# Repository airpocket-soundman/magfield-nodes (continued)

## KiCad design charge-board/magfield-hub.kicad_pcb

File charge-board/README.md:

# 充電ボード（ハブ）

ノード基板10台分の充電・監視・書き込みをまとめるボードです。KiCadファイル一式を追加済みですが、**まだ設計途中（WIP）で未発注**です。詳細は [DESIGN.md](DESIGN.md) を参照してください。

## ステータス（2026-10-30時点）

- 4層基板（100 × 96 mm）。現行ファイル（routed70）のDRCは、未接続1件（U2 TCA9535 の VCC）と CH6_STAT ビアのクリアランスエラー4件が残っています。
- U2周りの局部改版は試行済みですが、最良案は採用せず現行ファイルのままです。対処方針は DESIGN.md に記録しています。
- `wip/magfield-hub-u2rev19-WIP.kicad_pcb` は、そのU2改版の試行版（設計途中の作業ファイル）です。クリアランスエラーは0件まで解消しましたが、信号の未接続が6件残っており、現行ファイルには未反映です。

## 構成

- ホスト接続: M5Stack の Port A（Grove / I2C）。ボード自体にマイコンは載せない
- 充電チャンネル ×10: MCP73831（PROG抵抗で約40mA = LIR2032の1C）、チャンネルごとのカットオフ用MOSFETとステータスLED
- 制御・監視: TCA9535（I2C GPIOエクスパンダ）×2 でカットオフ制御とSTAT読み取り、74HC4067（アナログマルチプレクサ）+ ADS1115（I2C ADC）で全チャンネルの電池電圧を読み取り
  - 「充電を一瞬止めてから電圧を測る」ことで、80〜90%充電でのカットオフを電圧ベースで判定する
- 書き込み: UPDI入力を同様に切り替えて、選択したチャンネルのノードへ書き込み信号を送る
- 電源: 充電用5VはボードのUSB-C入力から（10ch合計約400mAのため、Port Aの5Vには頼らない）
- ノード接続: JST PH 4ピン ×10（1=GND / 2=VBAT充電 / 3=UPDI / 4=ID予備）— ノード基板側と同一の割り当て

## ファイル

- `magfield-hub.kicad_pro / .kicad_sch / .kicad_pcb` — KiCad 8 プロジェクト
- `DESIGN.md` — 設計仕様・判断記録・検証結果
- `hub-bom-jlcpcb.csv` / `hub-cpl-jlcpcb.csv` — JLCPCB PCBA用BOM・配置データ
- `gerbers/` — 製造用ガーバー（4層）

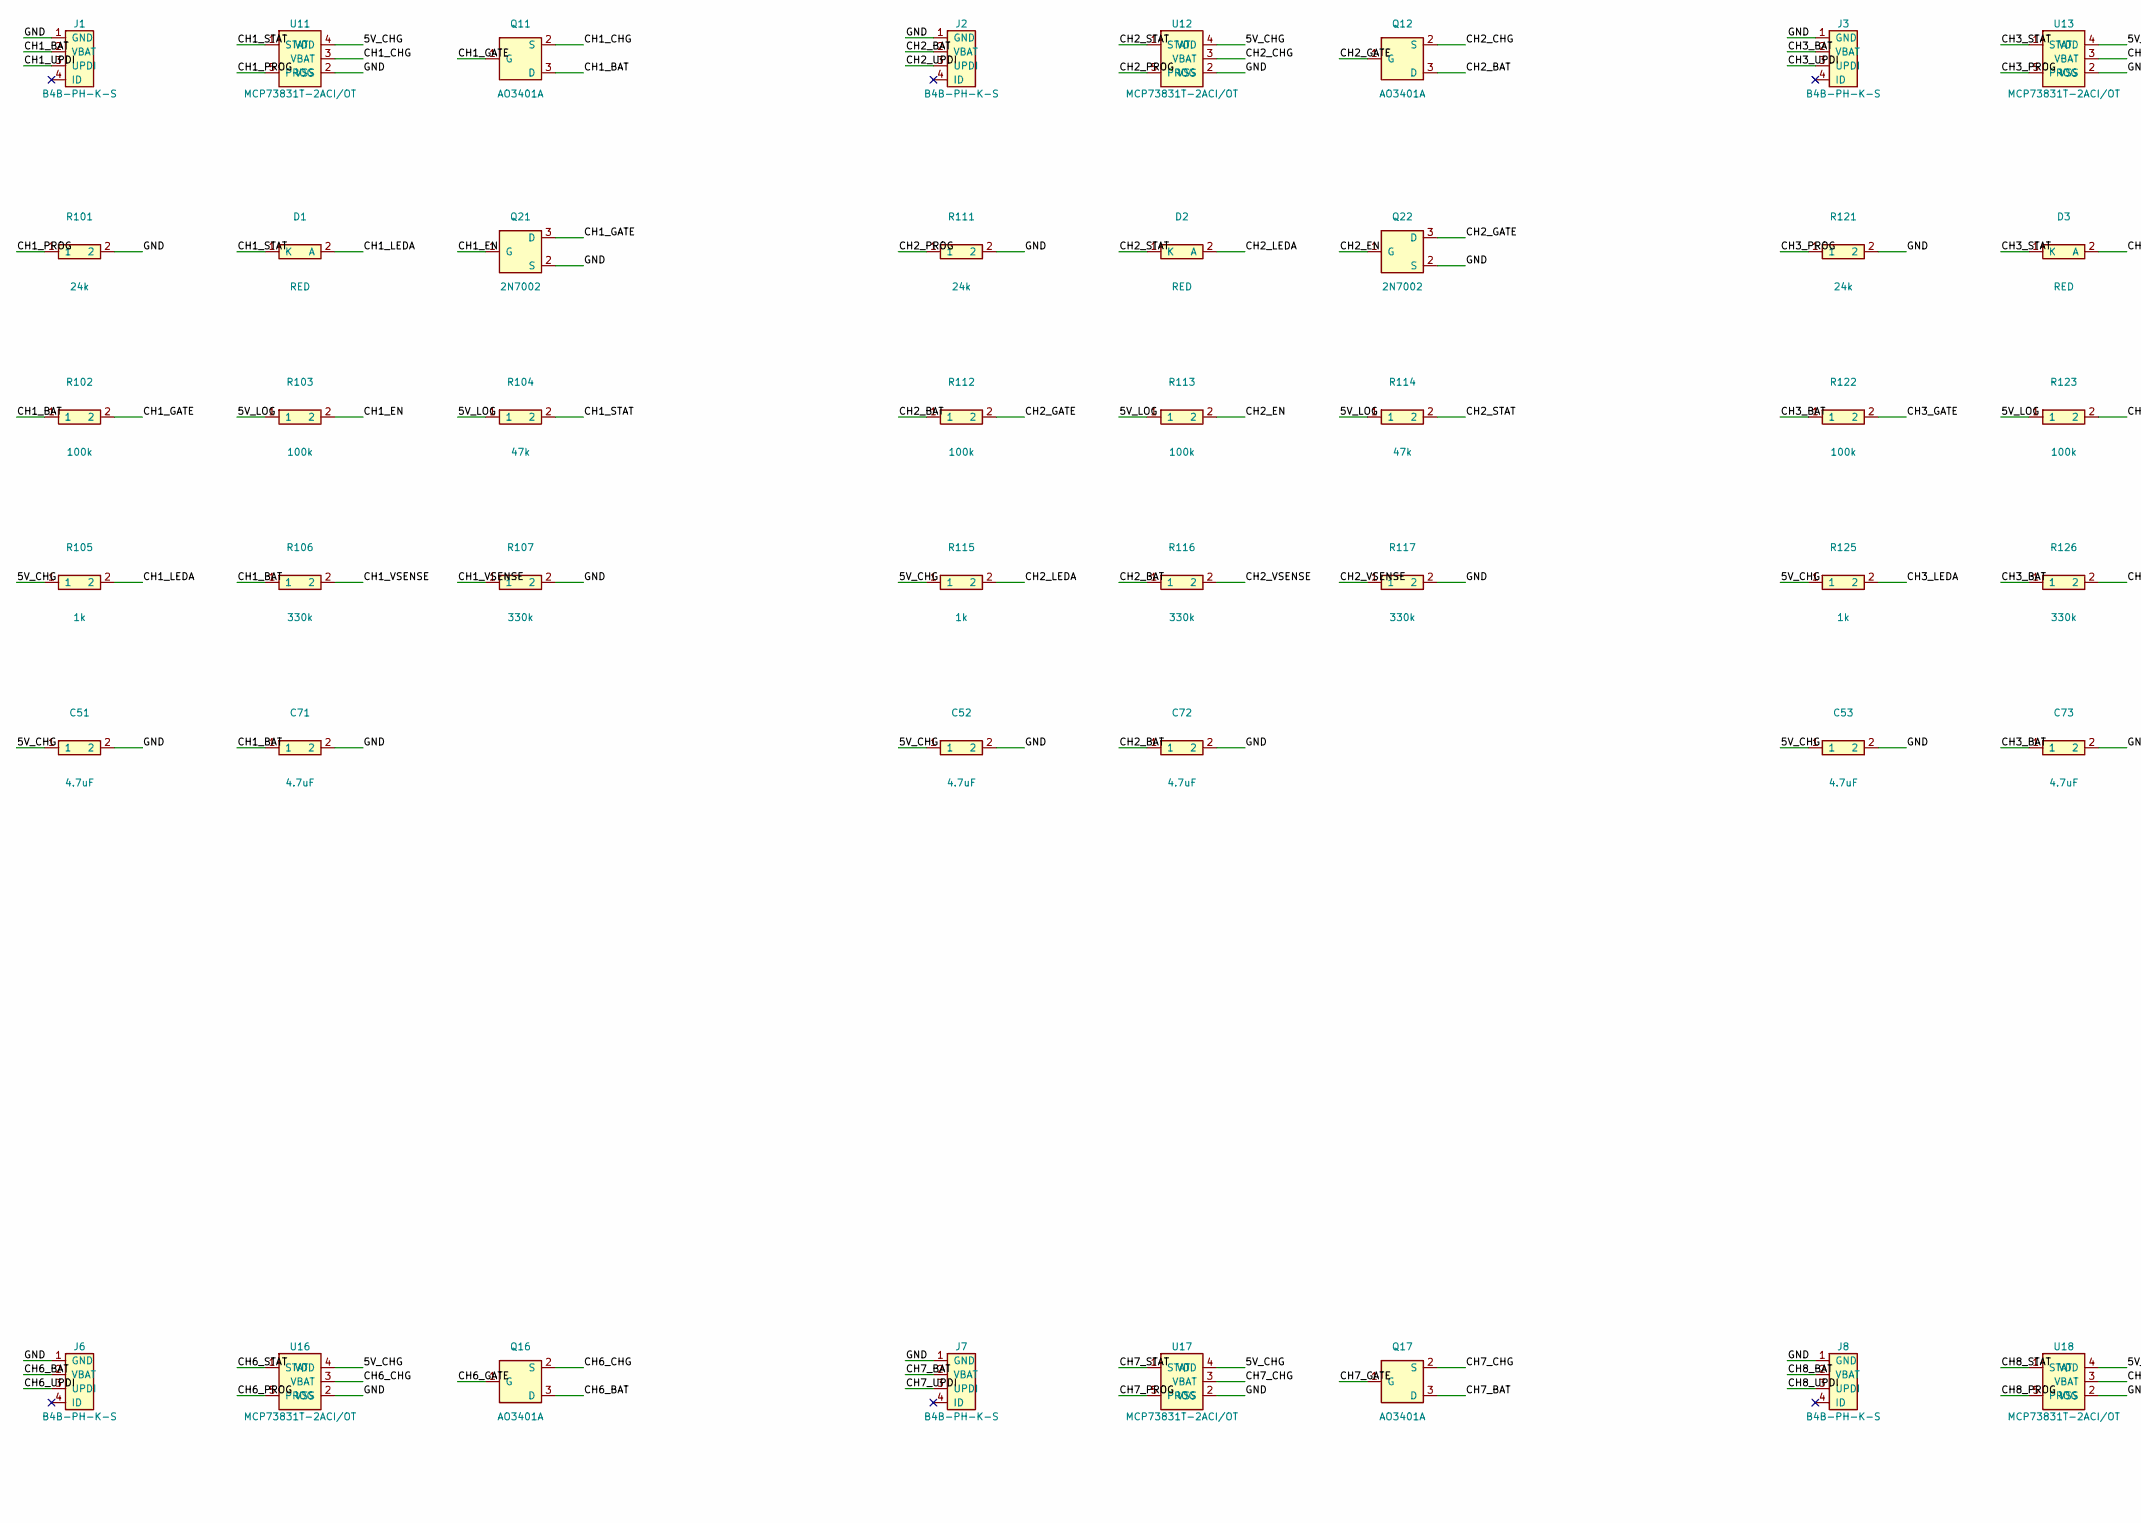
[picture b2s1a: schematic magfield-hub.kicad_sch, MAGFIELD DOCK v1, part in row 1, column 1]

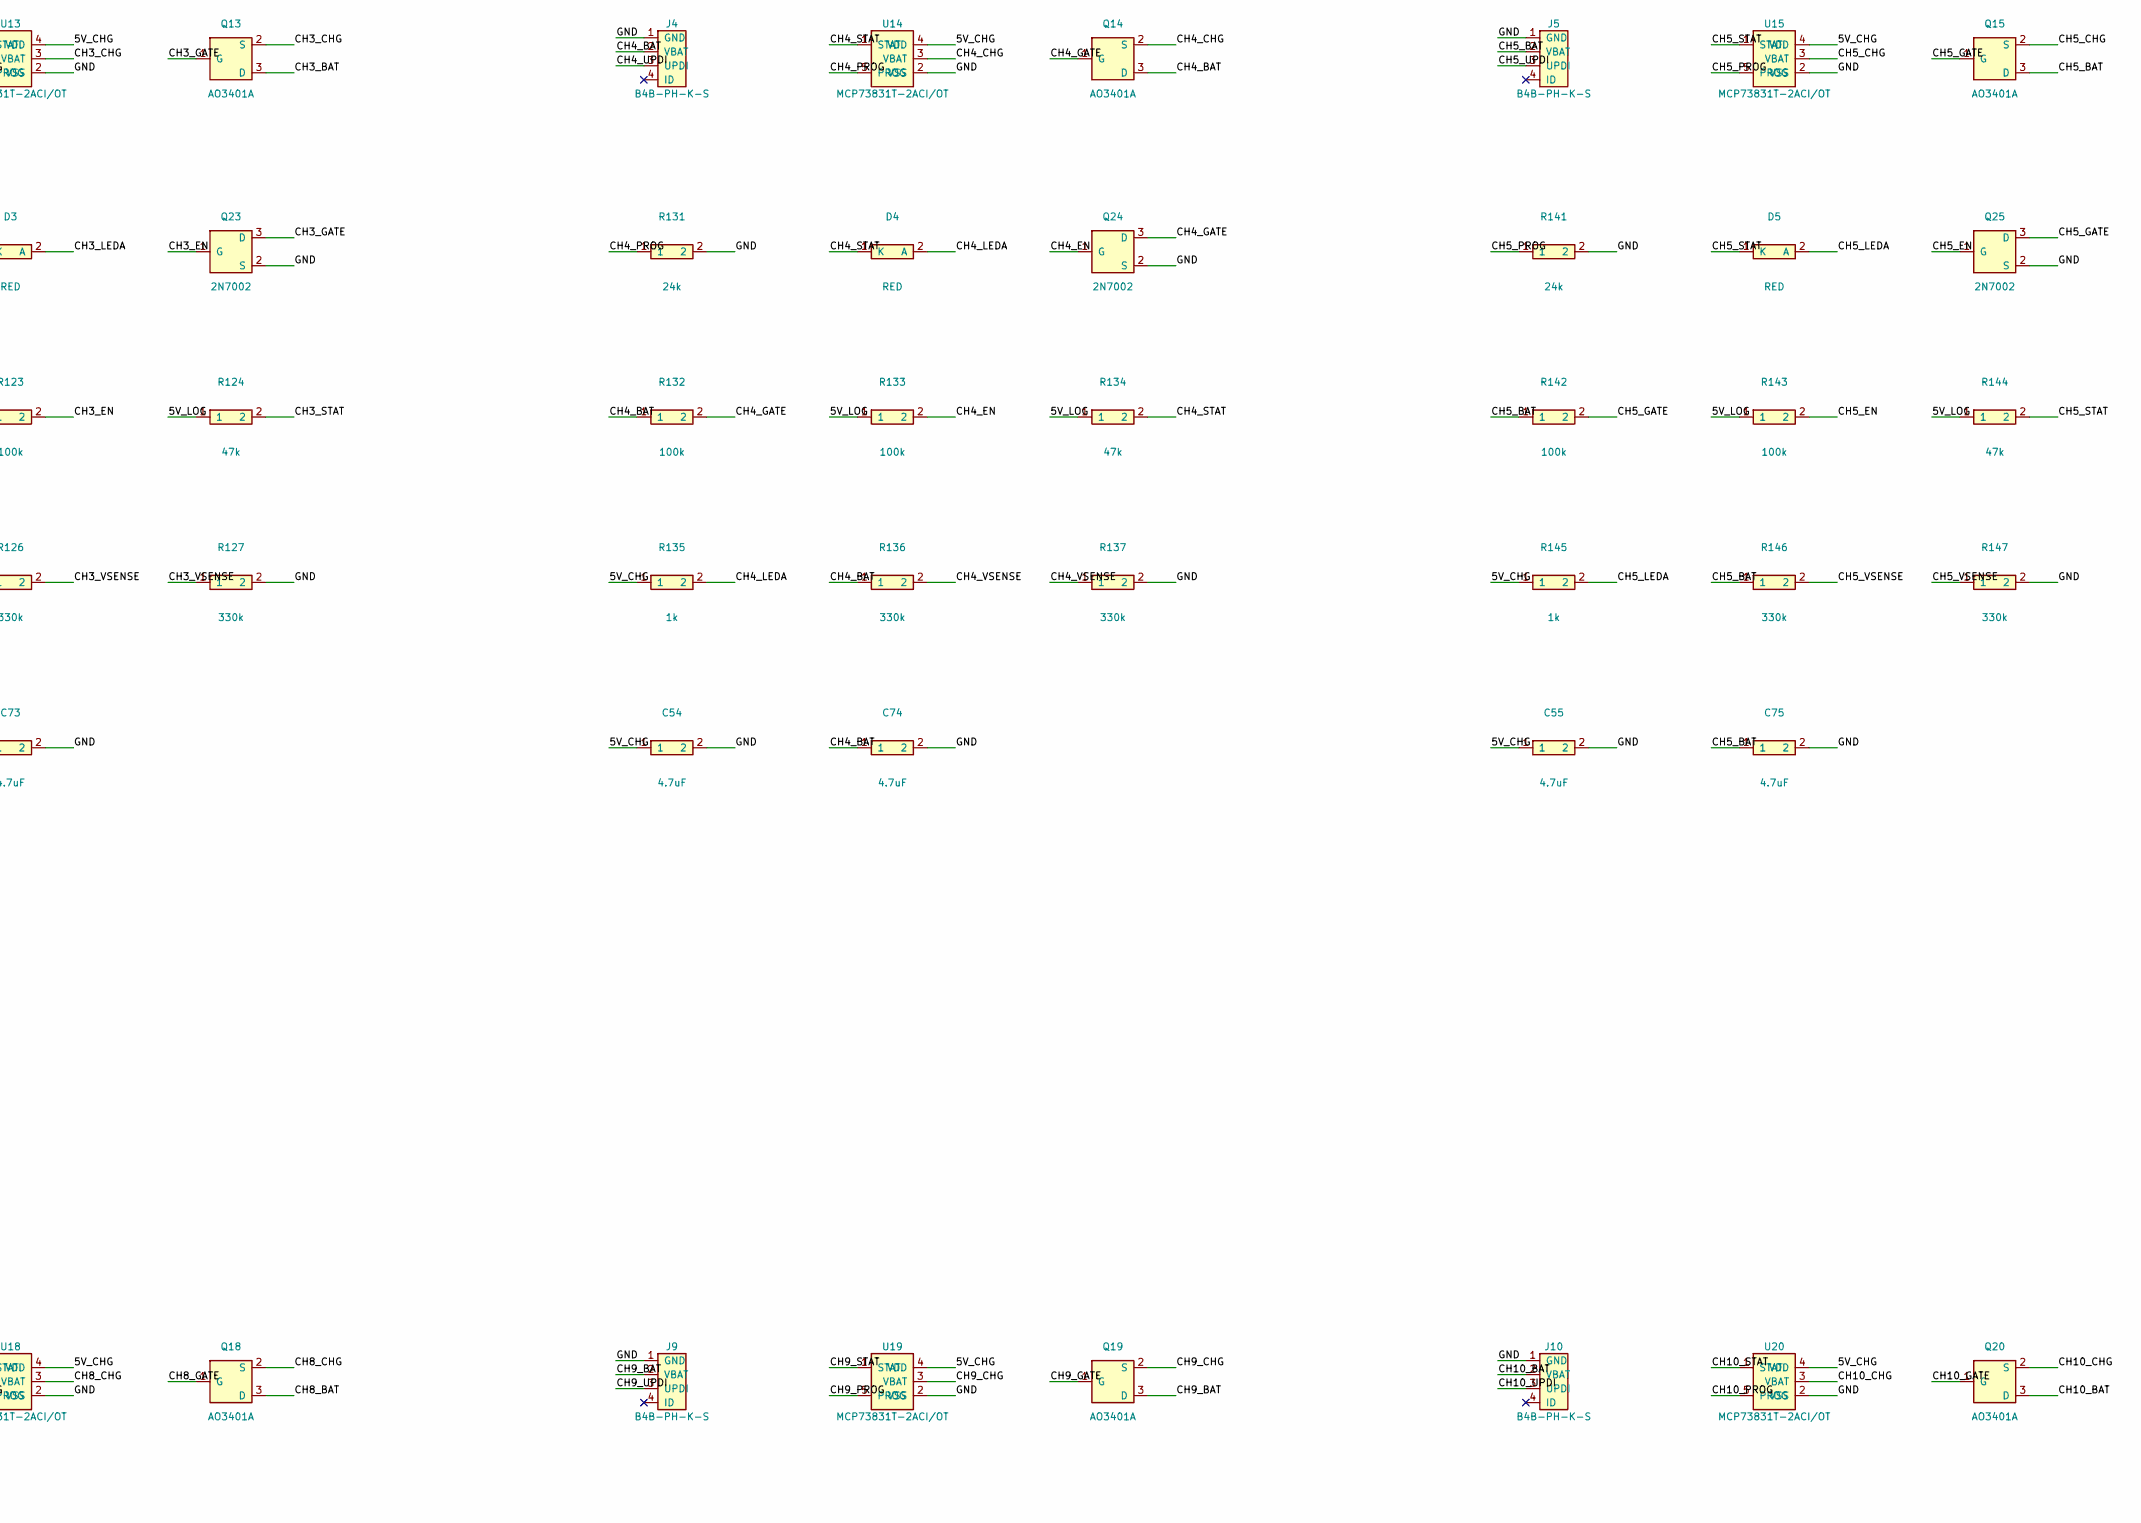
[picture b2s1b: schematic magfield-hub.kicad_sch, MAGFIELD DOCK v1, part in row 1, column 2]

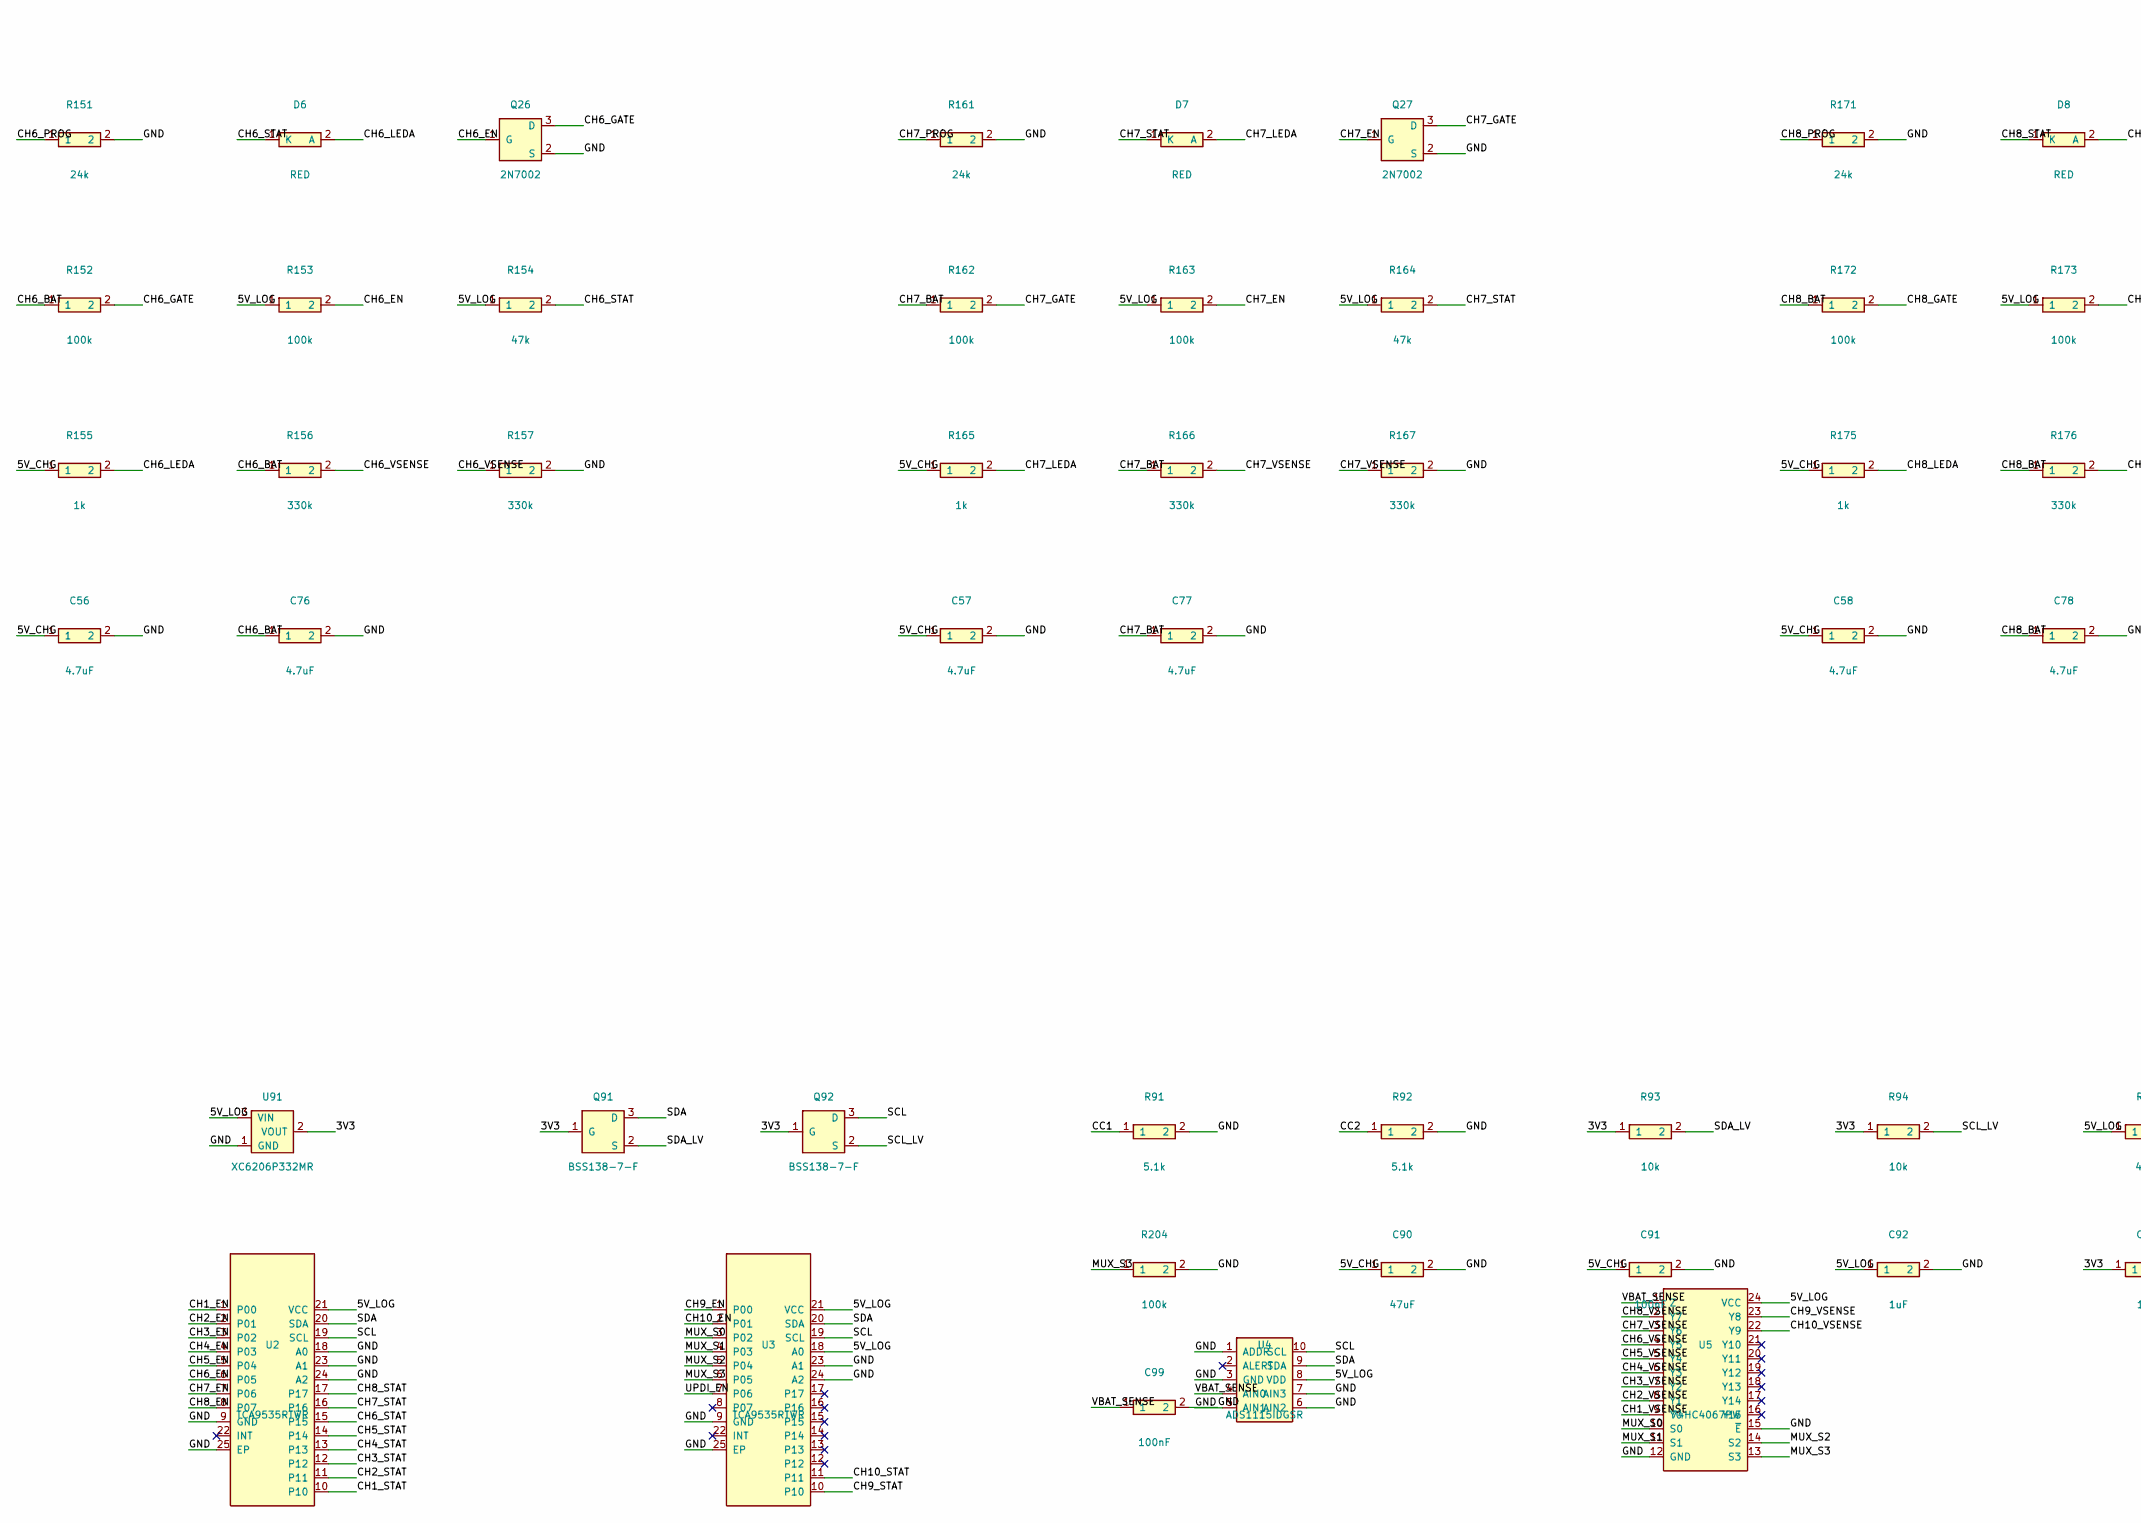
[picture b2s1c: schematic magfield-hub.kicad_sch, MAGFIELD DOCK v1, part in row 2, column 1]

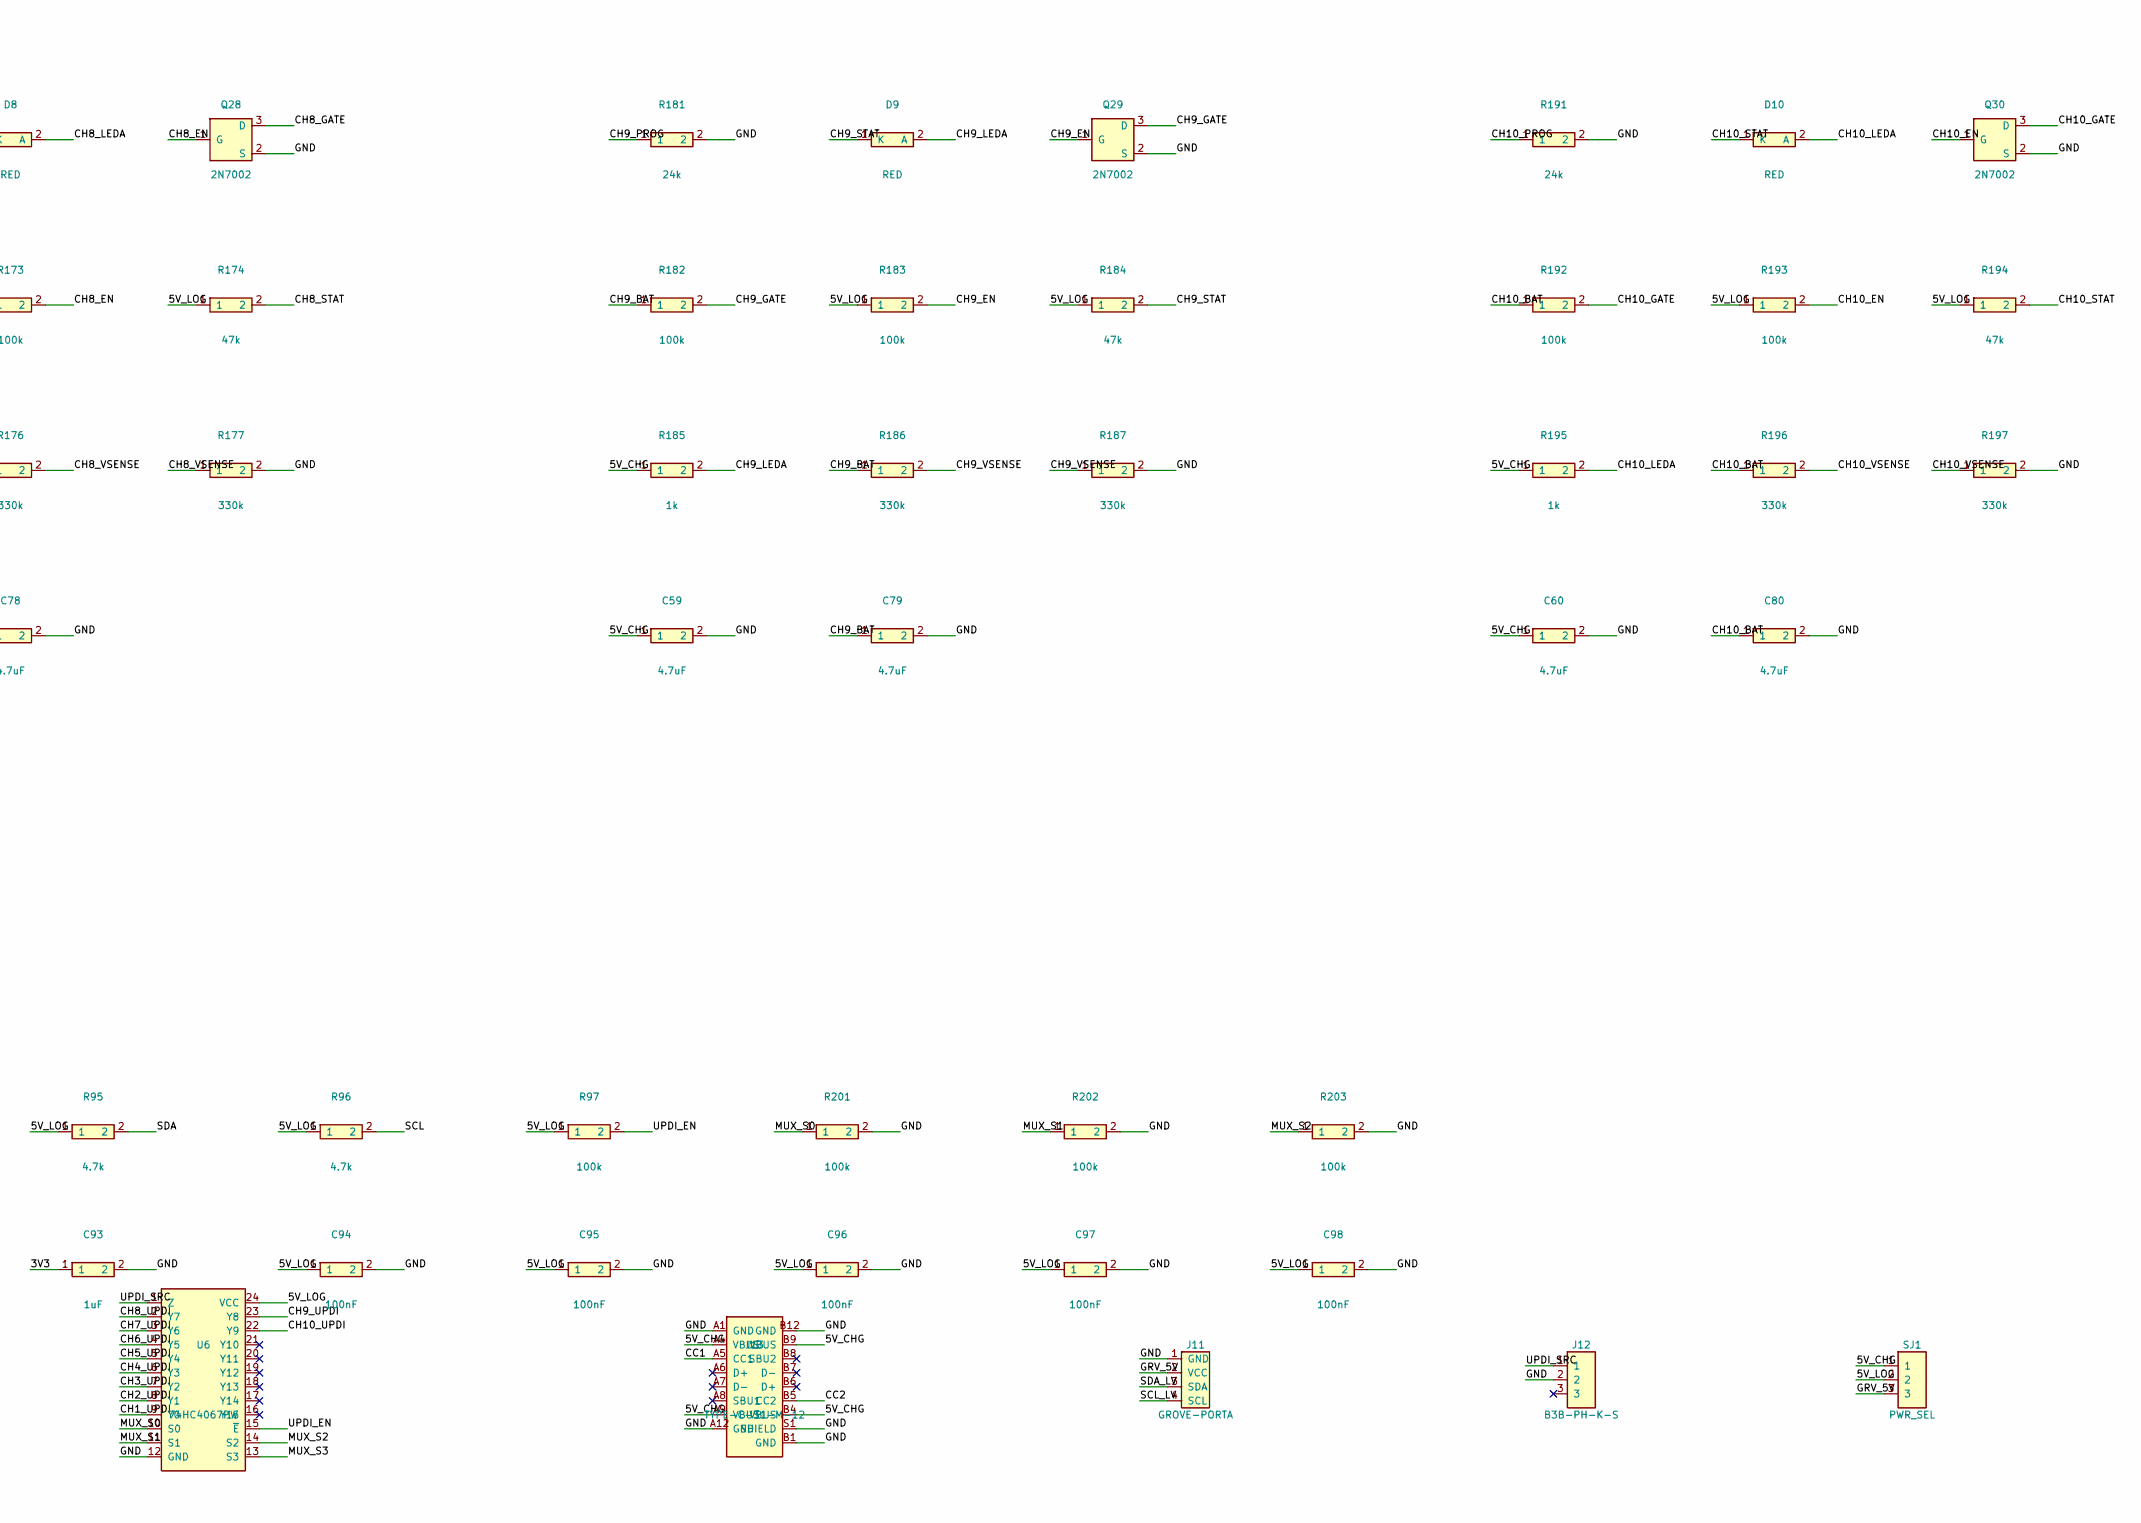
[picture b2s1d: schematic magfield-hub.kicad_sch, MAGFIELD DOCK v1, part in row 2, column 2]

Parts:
C51, C52, C53, C54, C55, C56, C57, C58, C59, C60, C71, C72, C73, C74, C75, C76, C77, C78, C79, C80: 4.7uF; C_0603_1608Metric; LCSC C19666
C90: 47uF; C_0805_2012Metric; LCSC C16780
C91, C94, C95, C96, C97, C98, C99: 100nF; C_0603_1608Metric; LCSC C14663
C92, C93: 1uF; C_0603_1608Metric; LCSC C15849
D1, D2, D3, D4, D5, D6, D7, D8, D9, D10: RED; LED_0603_1608Metric; LCSC C2286
J1, J2, J3, J4, J5, J6, J7, J8, J9, J10: B4B-PH-K-S; JST_PH_B4B-PH-K_1x04_P2.00mm_Vertical; LCSC C131334
J11: GROVE-PORTA; JST_PH_B4B-PH-K_1x04_P2.00mm_Vertical; LCSC C131334
J12: B3B-PH-K-S; JST_PH_B3B-PH-K_1x03_P2.00mm_Vertical; LCSC C131339
J13: TYPE-C-31-M-12; USB_C_Receptacle_HRO_TYPE-C-31-M-12; LCSC C165948
Q11, Q12, Q13, Q14, Q15, Q16, Q17, Q18, Q19, Q20: AO3401A; SOT-23; LCSC C15127
Q21, Q22, Q23, Q24, Q25, Q26, Q27, Q28, Q29, Q30: 2N7002; SOT-23; LCSC C8545
Q91, Q92: BSS138-7-F; SOT-23; LCSC C40912
R91, R92: 5.1k; R_0603_1608Metric; LCSC C23186
R93, R94: 10k; R_0603_1608Metric; LCSC C25804
R95, R96: 4.7k; R_0603_1608Metric; LCSC C23162
R97, R102, R103, R112, R113, R122, R123, R132, R133, R142, R143, R152, R153, R162, R163, R172, R173, R182, R183, R192, R193, R201, R202, R203, R204: 100k; R_0603_1608Metric; LCSC C25803
R101, R111, R121, R131, R141, R151, R161, R171, R181, R191: 24k; R_0603_1608Metric; LCSC C23352
R104, R114, R124, R134, R144, R154, R164, R174, R184, R194: 47k; R_0603_1608Metric; LCSC C25819
R105, R115, R125, R135, R145, R155, R165, R175, R185, R195: 1k; R_0603_1608Metric; LCSC C21190
R106, R107, R116, R117, R126, R127, R136, R137, R146, R147, R156, R157, R166, R167, R176, R177, R186, R187, R196, R197: 330k; R_0603_1608Metric; LCSC C23137
SJ1: PWR_SEL; SJ3
U2, U3: TCA9535RTWR; WQFN-24-1EP_4x4mm_P0.5mm_EP2.45x2.45mm; LCSC C129354
U4: ADS1115IDGSR; VSSOP-10_3x3mm_P0.5mm; LCSC C37593
U5, U6: 74HC4067PW; TSSOP-24_4.4x7.8mm_P0.65mm; LCSC C179326
U11, U12, U13, U14, U15, U16, U17, U18, U19, U20: MCP73831T-2ACI/OT; SOT-23-5; LCSC C424093
U91: XC6206P332MR; SOT-23; LCSC C5446

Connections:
3V3: C93.1, Q91.1 (G), Q92.1 (G), R93.1, R94.1, U91.2 (VOUT)
5V_CHG: C51.1, C52.1, C53.1, C54.1, C55.1, C56.1, C57.1, C58.1, C59.1, C60.1, C90.1, C91.1, J13.A4 (VBUS), J13.A9 (VBUS), J13.B4 (VBUS), J13.B9 (VBUS), R105.1, R115.1, R125.1, R135.1, R145.1, R155.1, R165.1, R175.1, R185.1, R195.1, SJ1.1, U11.4 (VDD), U12.4 (VDD), U13.4 (VDD), U14.4 (VDD), U15.4 (VDD), U16.4 (VDD), U17.4 (VDD), U18.4 (VDD), U19.4 (VDD), U20.4 (VDD)
5V_LOG: C92.1, C94.1, C95.1, C96.1, C97.1, C98.1, R95.1, R96.1, R97.1, R103.1, R104.1, R113.1, R114.1, R123.1, R124.1, R133.1, R134.1, R143.1, R144.1, R153.1, R154.1, R163.1, R164.1, R173.1, R174.1, R183.1, R184.1, R193.1, R194.1, SJ1.2, U2.21 (VCC), U3.18 (A0), U3.21 (VCC), U4.8 (VDD), U5.24 (VCC), U6.24 (VCC), U91.3 (VIN)
CC1: J13.A5 (CC1), R91.1
CC2: J13.B5 (CC2), R92.1
CH1_BAT: C71.1, J1.2 (VBAT), Q11.3 (D), R102.1, R106.1
CH1_CHG: Q11.2 (S), U11.3 (VBAT)
CH1_EN: Q21.1 (G), R103.2, U2.1 (P00)
CH1_GATE: Q11.1 (G), Q21.3 (D), R102.2
CH1_LEDA: D1.2 (A), R105.2
CH1_PROG: R101.1, U11.5 (PROG)
CH1_STAT: D1.1 (K), R104.2, U2.10, U11.1 (STAT)
CH1_UPDI: J1.3 (UPDI), U6.9 (Y0)
CH1_VSENSE: R106.2, R107.1, U5.9 (Y0)
CH2_BAT: C72.1, J2.2 (VBAT), Q12.3 (D), R112.1, R116.1
CH2_CHG: Q12.2 (S), U12.3 (VBAT)
CH2_EN: Q22.1 (G), R113.2, U2.2 (P01)
CH2_GATE: Q12.1 (G), Q22.3 (D), R112.2
CH2_LEDA: D2.2 (A), R115.2
CH2_PROG: R111.1, U12.5 (PROG)
CH2_STAT: D2.1 (K), R114.2, U2.11, U12.1 (STAT)
CH2_UPDI: J2.3 (UPDI), U6.8 (Y1)
CH2_VSENSE: R116.2, R117.1, U5.8 (Y1)
CH3_BAT: C73.1, J3.2 (VBAT), Q13.3 (D), R122.1, R126.1
CH3_CHG: Q13.2 (S), U13.3 (VBAT)
CH3_EN: Q23.1 (G), R123.2, U2.3 (P02)
CH3_GATE: Q13.1 (G), Q23.3 (D), R122.2
CH3_LEDA: D3.2 (A), R125.2
CH3_PROG: R121.1, U13.5 (PROG)
CH3_STAT: D3.1 (K), R124.2, U2.12, U13.1 (STAT)
CH3_UPDI: J3.3 (UPDI), U6.7 (Y2)
CH3_VSENSE: R126.2, R127.1, U5.7 (Y2)
CH4_BAT: C74.1, J4.2 (VBAT), Q14.3 (D), R132.1, R136.1
CH4_CHG: Q14.2 (S), U14.3 (VBAT)
CH4_EN: Q24.1 (G), R133.2, U2.4 (P03)
CH4_GATE: Q14.1 (G), Q24.3 (D), R132.2
CH4_LEDA: D4.2 (A), R135.2
CH4_PROG: R131.1, U14.5 (PROG)
CH4_STAT: D4.1 (K), R134.2, U2.13, U14.1 (STAT)
CH4_UPDI: J4.3 (UPDI), U6.6 (Y3)
CH4_VSENSE: R136.2, R137.1, U5.6 (Y3)
CH5_BAT: C75.1, J5.2 (VBAT), Q15.3 (D), R142.1, R146.1
CH5_CHG: Q15.2 (S), U15.3 (VBAT)
CH5_EN: Q25.1 (G), R143.2, U2.5 (P04)
CH5_GATE: Q15.1 (G), Q25.3 (D), R142.2
CH5_LEDA: D5.2 (A), R145.2
CH5_PROG: R141.1, U15.5 (PROG)
CH5_STAT: D5.1 (K), R144.2, U2.14, U15.1 (STAT)
CH5_UPDI: J5.3 (UPDI), U6.5 (Y4)
CH5_VSENSE: R146.2, R147.1, U5.5 (Y4)
CH6_BAT: C76.1, J6.2 (VBAT), Q16.3 (D), R152.1, R156.1
CH6_CHG: Q16.2 (S), U16.3 (VBAT)
CH6_EN: Q26.1 (G), R153.2, U2.6 (P05)
CH6_GATE: Q16.1 (G), Q26.3 (D), R152.2
CH6_LEDA: D6.2 (A), R155.2
CH6_PROG: R151.1, U16.5 (PROG)
CH6_STAT: D6.1 (K), R154.2, U2.15, U16.1 (STAT)
CH6_UPDI: J6.3 (UPDI), U6.4 (Y5)
CH6_VSENSE: R156.2, R157.1, U5.4 (Y5)
CH7_BAT: C77.1, J7.2 (VBAT), Q17.3 (D), R162.1, R166.1
CH7_CHG: Q17.2 (S), U17.3 (VBAT)
CH7_EN: Q27.1 (G), R163.2, U2.7 (P06)
CH7_GATE: Q17.1 (G), Q27.3 (D), R162.2
CH7_LEDA: D7.2 (A), R165.2
CH7_PROG: R161.1, U17.5 (PROG)
CH7_STAT: D7.1 (K), R164.2, U2.16, U17.1 (STAT)
CH7_UPDI: J7.3 (UPDI), U6.3 (Y6)
CH7_VSENSE: R166.2, R167.1, U5.3 (Y6)
CH8_BAT: C78.1, J8.2 (VBAT), Q18.3 (D), R172.1, R176.1
CH8_CHG: Q18.2 (S), U18.3 (VBAT)
CH8_EN: Q28.1 (G), R173.2, U2.8 (P07)
CH8_GATE: Q18.1 (G), Q28.3 (D), R172.2
CH8_LEDA: D8.2 (A), R175.2
CH8_PROG: R171.1, U18.5 (PROG)
CH8_STAT: D8.1 (K), R174.2, U2.17, U18.1 (STAT)
CH8_UPDI: J8.3 (UPDI), U6.2 (Y7)
CH8_VSENSE: R176.2, R177.1, U5.2 (Y7)
CH9_BAT: C79.1, J9.2 (VBAT), Q19.3 (D), R182.1, R186.1
CH9_CHG: Q19.2 (S), U19.3 (VBAT)
CH9_EN: Q29.1 (G), R183.2, U3.1 (P00)
CH9_GATE: Q19.1 (G), Q29.3 (D), R182.2
CH9_LEDA: D9.2 (A), R185.2
CH9_PROG: R181.1, U19.5 (PROG)
CH9_STAT: D9.1 (K), R184.2, U3.10, U19.1 (STAT)
CH9_UPDI: J9.3 (UPDI), U6.23 (Y8)
CH9_VSENSE: R186.2, R187.1, U5.23 (Y8)
CH10_BAT: C80.1, J10.2 (VBAT), Q20.3 (D), R192.1, R196.1
CH10_CHG: Q20.2 (S), U20.3 (VBAT)
CH10_EN: Q30.1 (G), R193.2, U3.2 (P01)
CH10_GATE: Q20.1 (G), Q30.3 (D), R192.2
CH10_LEDA: D10.2 (A), R195.2
CH10_PROG: R191.1, U20.5 (PROG)
CH10_STAT: D10.1 (K), R194.2, U3.11, U20.1 (STAT)
CH10_UPDI: J10.3 (UPDI), U6.22 (Y9)
CH10_VSENSE: R196.2, R197.1, U5.22 (Y9)
GND: C51.2, C52.2, C53.2, C54.2, C55.2, C56.2, C57.2, C58.2, C59.2, C60.2, C71.2, C72.2, C73.2, C74.2, C75.2, C76.2, C77.2, C78.2, C79.2, C80.2, C90.2, C91.2, C92.2, C93.2, C94.2, C95.2, C96.2, C97.2, C98.2, C99.2, J1.1 (GND), J2.1 (GND), J3.1 (GND), J4.1 (GND), J5.1 (GND), J6.1 (GND), J7.1 (GND), J8.1 (GND), J9.1 (GND), J10.1 (GND), J11.1 (GND), J12.2, J13.A1 (GND), J13.A12 (GND), J13.B1 (GND), J13.B12 (GND), J13.S1 (SHIELD), Q21.2 (S), Q22.2 (S), Q23.2 (S), Q24.2 (S), Q25.2 (S), Q26.2 (S), Q27.2 (S), Q28.2 (S), Q29.2 (S), Q30.2 (S), R91.2, R92.2, R101.2, R107.2, R111.2, R117.2, R121.2, R127.2, R131.2, R137.2, R141.2, R147.2, R151.2, R157.2, R161.2, R167.2, R171.2, R177.2, R181.2, R187.2, R191.2, R197.2, R201.2, R202.2, R203.2, R204.2, U2.9 (GND), U2.18 (A0), U2.23 (A1), U2.24 (A2), U2.25 (EP), U3.9 (GND), U3.23 (A1), U3.24 (A2), U3.25 (EP), U4.1 (ADDR), U4.3 (GND), U4.5 (AIN1), U4.6 (AIN2), U4.7 (AIN3), U5.12 (GND), U5.15 (~E), U6.12 (GND), U11.2 (VSS), U12.2 (VSS), U13.2 (VSS), U14.2 (VSS), U15.2 (VSS), U16.2 (VSS), U17.2 (VSS), U18.2 (VSS), U19.2 (VSS), U20.2 (VSS), U91.1 (GND)
GRV_5V: J11.2 (VCC), SJ1.3
MUX_S0: R201.1, U3.3 (P02), U5.10 (S0), U6.10 (S0)
MUX_S1: R202.1, U3.4 (P03), U5.11 (S1), U6.11 (S1)
MUX_S2: R203.1, U3.5 (P04), U5.14 (S2), U6.14 (S2)
MUX_S3: R204.1, U3.6 (P05), U5.13 (S3), U6.13 (S3)
SCL: Q92.3 (D), R96.2, U2.19 (SCL), U3.19 (SCL), U4.10 (SCL)
SCL_LV: J11.4 (SCL), Q92.2 (S), R94.2
SDA: Q91.3 (D), R95.2, U2.20 (SDA), U3.20 (SDA), U4.9 (SDA)
SDA_LV: J11.3 (SDA), Q91.2 (S), R93.2
UPDI_EN: R97.2, U3.7 (P06), U6.15 (~E)
UPDI_SRC: J12.1, U6.1 (Z)
VBAT_SENSE: C99.1, U4.4 (AIN0), U5.1 (Z)

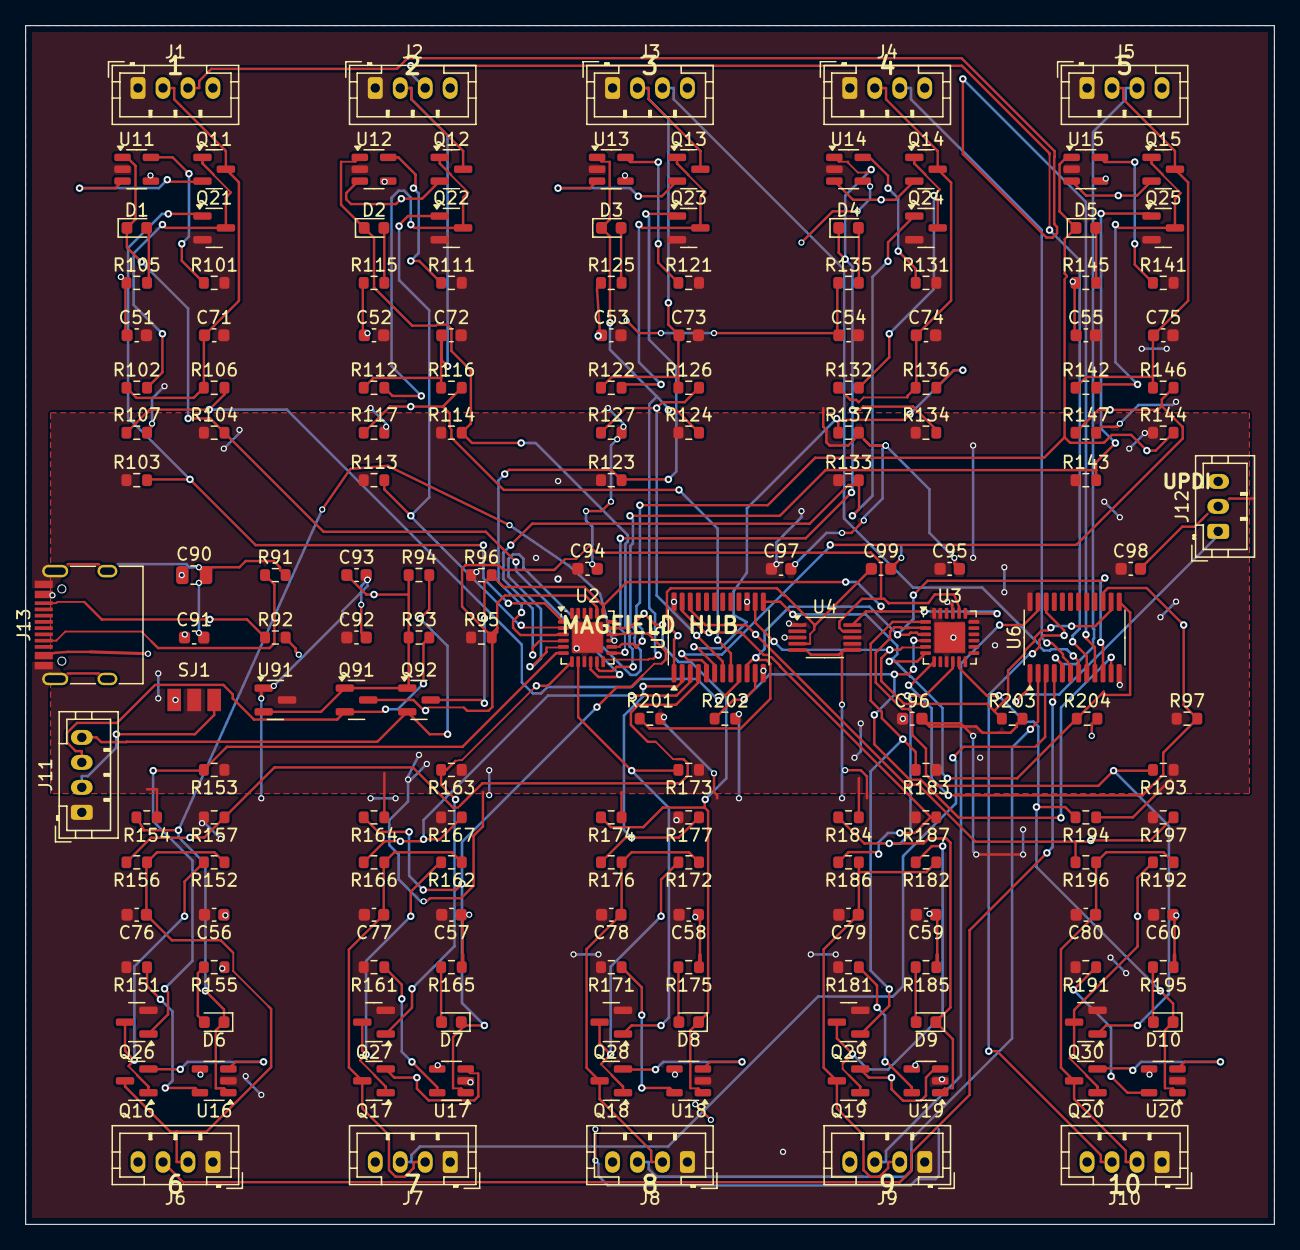
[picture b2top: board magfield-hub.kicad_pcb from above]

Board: 4 copper layers, 100.0 x 96.0 mm, 173 parts (0 on the bottom side), 108 nets.

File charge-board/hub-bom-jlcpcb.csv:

Comment,Designator,Footprint,LCSC Part #,Quantity
4.7uF,"C51,C52,C53,C54,C55,C56,C57,C58,C59,C60,C71,C72,C73,C74,C75,C76,C77,C78,C79,C80",C_0603_1608Metric,C19666,20
47uF,C90,C_0805_2012Metric,C16780,1
100nF,"C91,C94,C95,C96,C97,C98,C99",C_0603_1608Metric,C14663,7
1uF,"C92,C93",C_0603_1608Metric,C15849,2
RED,"D1,D2,D3,D4,D5,D6,D7,D8,D9,D10",LED_0603_1608Metric,C2286,10
B4B-PH-K-S,"J1,J2,J3,J4,J5,J6,J7,J8,J9,J10",JST_PH_B4B-PH-K_1x04_P2.00mm_Vertical,C131334,10
GROVE-PORTA,J11,JST_PH_B4B-PH-K_1x04_P2.00mm_Vertical,C131334,1
B3B-PH-K-S,J12,JST_PH_B3B-PH-K_1x03_P2.00mm_Vertical,C131339,1
TYPE-C-31-M-12,J13,USB_C_Receptacle_HRO_TYPE-C-31-M-12,C165948,1
AO3401A,"Q11,Q12,Q13,Q14,Q15,Q16,Q17,Q18,Q19,Q20",SOT-23,C15127,10
2N7002,"Q21,Q22,Q23,Q24,Q25,Q26,Q27,Q28,Q29,Q30",SOT-23,C8545,10
BSS138-7-F,"Q91,Q92",SOT-23,C40912,2
5.1k,"R91,R92",R_0603_1608Metric,C23186,2
10k,"R93,R94",R_0603_1608Metric,C25804,2
4.7k,"R95,R96",R_0603_1608Metric,C23162,2
100k,"R97,R102,R103,R112,R113,R122,R123,R132,R133,R142,R143,R152,R153,R162,R163,R172,R173,R182,R183,R192,R193,R201,R202,R203,R204",R_0603_1608Metric,C25803,25
24k,"R101,R111,R121,R131,R141,R151,R161,R171,R181,R191",R_0603_1608Metric,C23352,10
47k,"R104,R114,R124,R134,R144,R154,R164,R174,R184,R194",R_0603_1608Metric,C25819,10
1k,"R105,R115,R125,R135,R145,R155,R165,R175,R185,R195",R_0603_1608Metric,C21190,10
330k,"R106,R107,R116,R117,R126,R127,R136,R137,R146,R147,R156,R157,R166,R167,R176,R177,R186,R187,R196,R197",R_0603_1608Metric,C23137,20
PWR_SEL,SJ1,SJ3,,1
TCA9535RTWR,"U2,U3",WQFN-24-1EP_4x4mm_P0.5mm_EP2.45x2.45mm,C129354,2
ADS1115IDGSR,U4,VSSOP-10_3x3mm_P0.5mm,C37593,1
74HC4067PW,"U5,U6",TSSOP-24_4.4x7.8mm_P0.65mm,C179326,2
MCP73831T-2ACI/OT,"U11,U12,U13,U14,U15,U16,U17,U18,U19,U20",SOT-23-5,C424093,10
XC6206P332MR,U91,SOT-23,C5446,1
